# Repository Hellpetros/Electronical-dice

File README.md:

# Electronical-dice
Electronical dice made as school project.

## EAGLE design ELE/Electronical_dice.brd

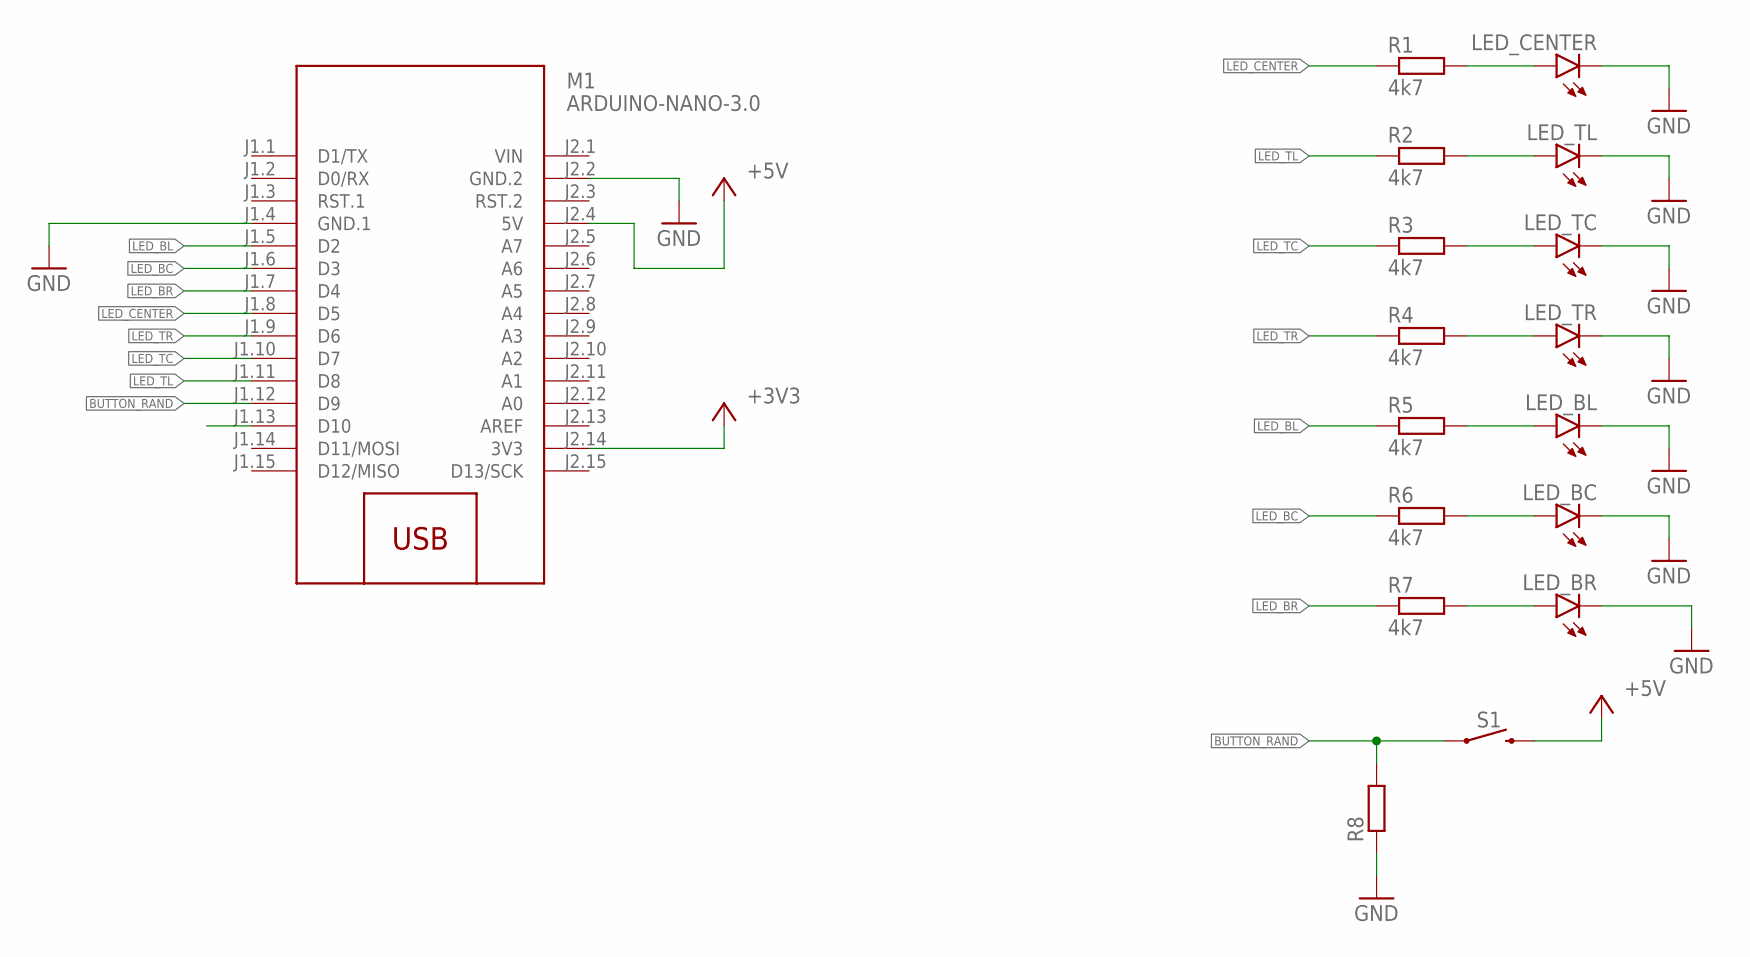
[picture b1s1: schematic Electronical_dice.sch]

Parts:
LED_BC: LED_RADIAL_RED; LEDRD254W60D565H860B
LED_BL: LED_RADIAL_RED; LEDRD254W60D565H860B
LED_BR: LED_RADIAL_RED; LEDRD254W60D565H860B
LED_CENTER: LED_RADIAL_RED; LEDRD254W60D565H860B
LED_TC: LED_RADIAL_RED; LEDRD254W60D565H860B
LED_TL: LED_RADIAL_RED; LEDRD254W60D565H860B
LED_TR: LED_RADIAL_RED; LEDRD254W60D565H860B
M1: ARDUINO-NANO-3.0
R1, R2, R3, R4, R5, R6, R7: 4k7; 0207/7
R8: R-EU_0207/7; 0207/7
S1: TACTILE_SWITCH_PTH_6.0MM

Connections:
+3V3: M1.J2.14 (3V3)
+5V: M1.J2.4 (5V), S1.3 (2)
BUTTON_RAND: M1.J1.12 (D9), R8.2, S1.1
GND: LED_BC.2 (C), LED_BL.2 (C), LED_BR.2 (C), LED_CENTER.2 (C), LED_TC.2 (C), LED_TL.2 (C), LED_TR.2 (C), M1.J1.4 (GND.1), M1.J2.2 (GND.2), R8.1
LED_BC: M1.J1.6 (D3), R6.1
LED_BL: M1.J1.5 (D2), R5.1
LED_BR: M1.J1.7 (D4), R7.1
LED_CENTER: M1.J1.8 (D5), R1.1
LED_TC: M1.J1.10 (D7), R3.1
LED_TL: M1.J1.11 (D8), R2.1
LED_TR: M1.J1.9 (D6), R4.1
unnamed: LED_CENTER.1 (A), R1.2
unnamed: LED_TL.1 (A), R2.2
unnamed: LED_TC.1 (A), R3.2
unnamed: LED_TR.1 (A), R4.2
unnamed: LED_BL.1 (A), R5.2
unnamed: LED_BC.1 (A), R6.2
unnamed: LED_BR.1 (A), R7.2
VIN: M1.J2.1 (VIN)

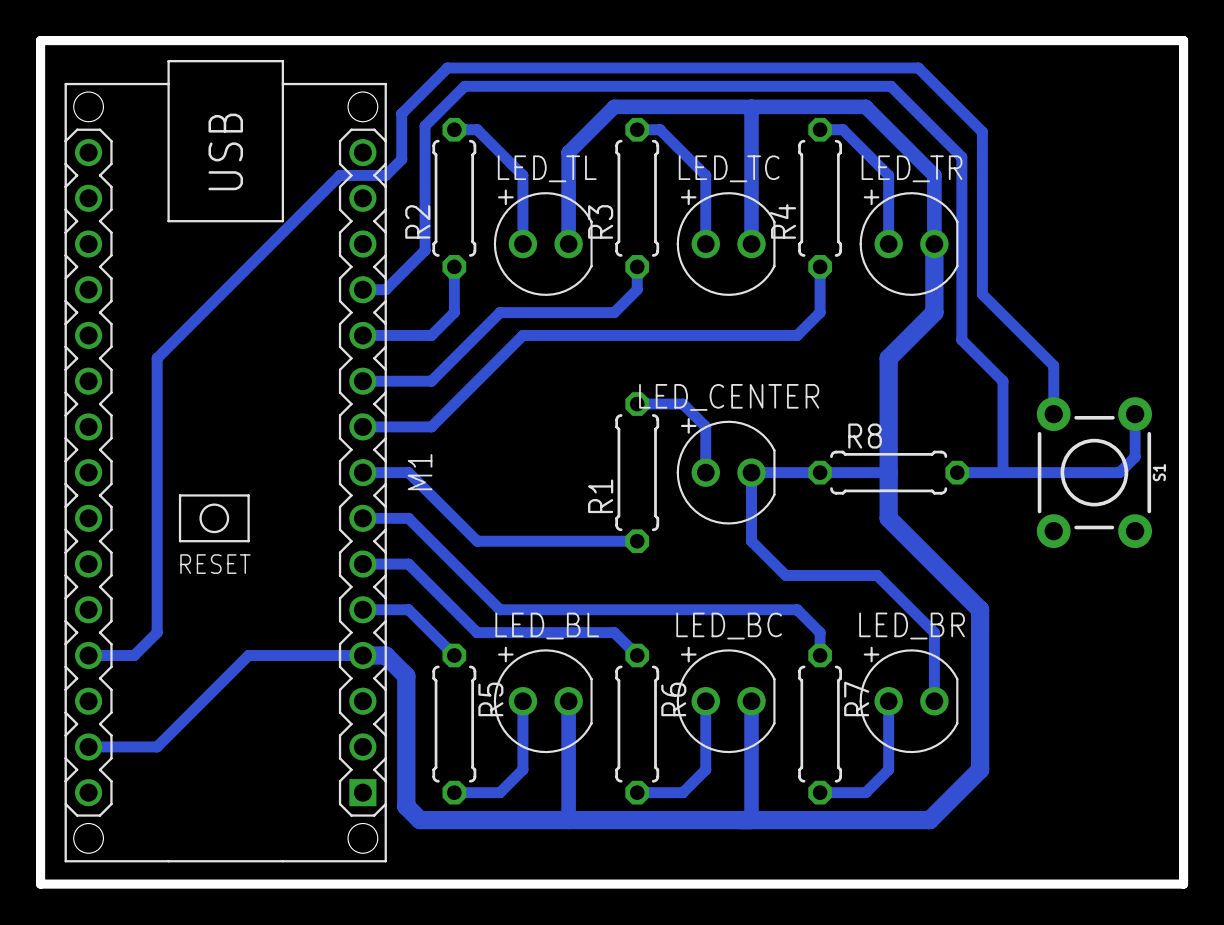
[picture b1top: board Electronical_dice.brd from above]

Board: 2 copper layers, 63.5 x 46.9 mm, 17 parts (0 on the bottom side), 17 nets.

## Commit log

2020-06-11 Add ELE & SOFTWARE files

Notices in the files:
parts and their libraries:
diy-modules: Released under the Creative Commons Attribution 4.0 International License: http://creativecommons.org/licenses/by/4.0
SparkFun-Switches: Licensing: Creative Commons ShareAlike 4.0 International - https://creativecommons.org/licenses/by-sa/4.0
